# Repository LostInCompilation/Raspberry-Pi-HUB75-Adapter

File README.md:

# Raspberry Pi Zero HUB75 LED-Matrix Controller / Adapter

## Features
- Everything on board
- 2 parralel chains of LED-Matrix panels (each chain can habe many panels)
- Suppport for HUB75 and HUB75E (ABCD**E** address lines)
- Power for LED-Matrix panels comes from board
- I2C extension port for custom hardware (light sensor, accelrometer, ...)
- Reverse polarity protection

## 3D Board view

## Board

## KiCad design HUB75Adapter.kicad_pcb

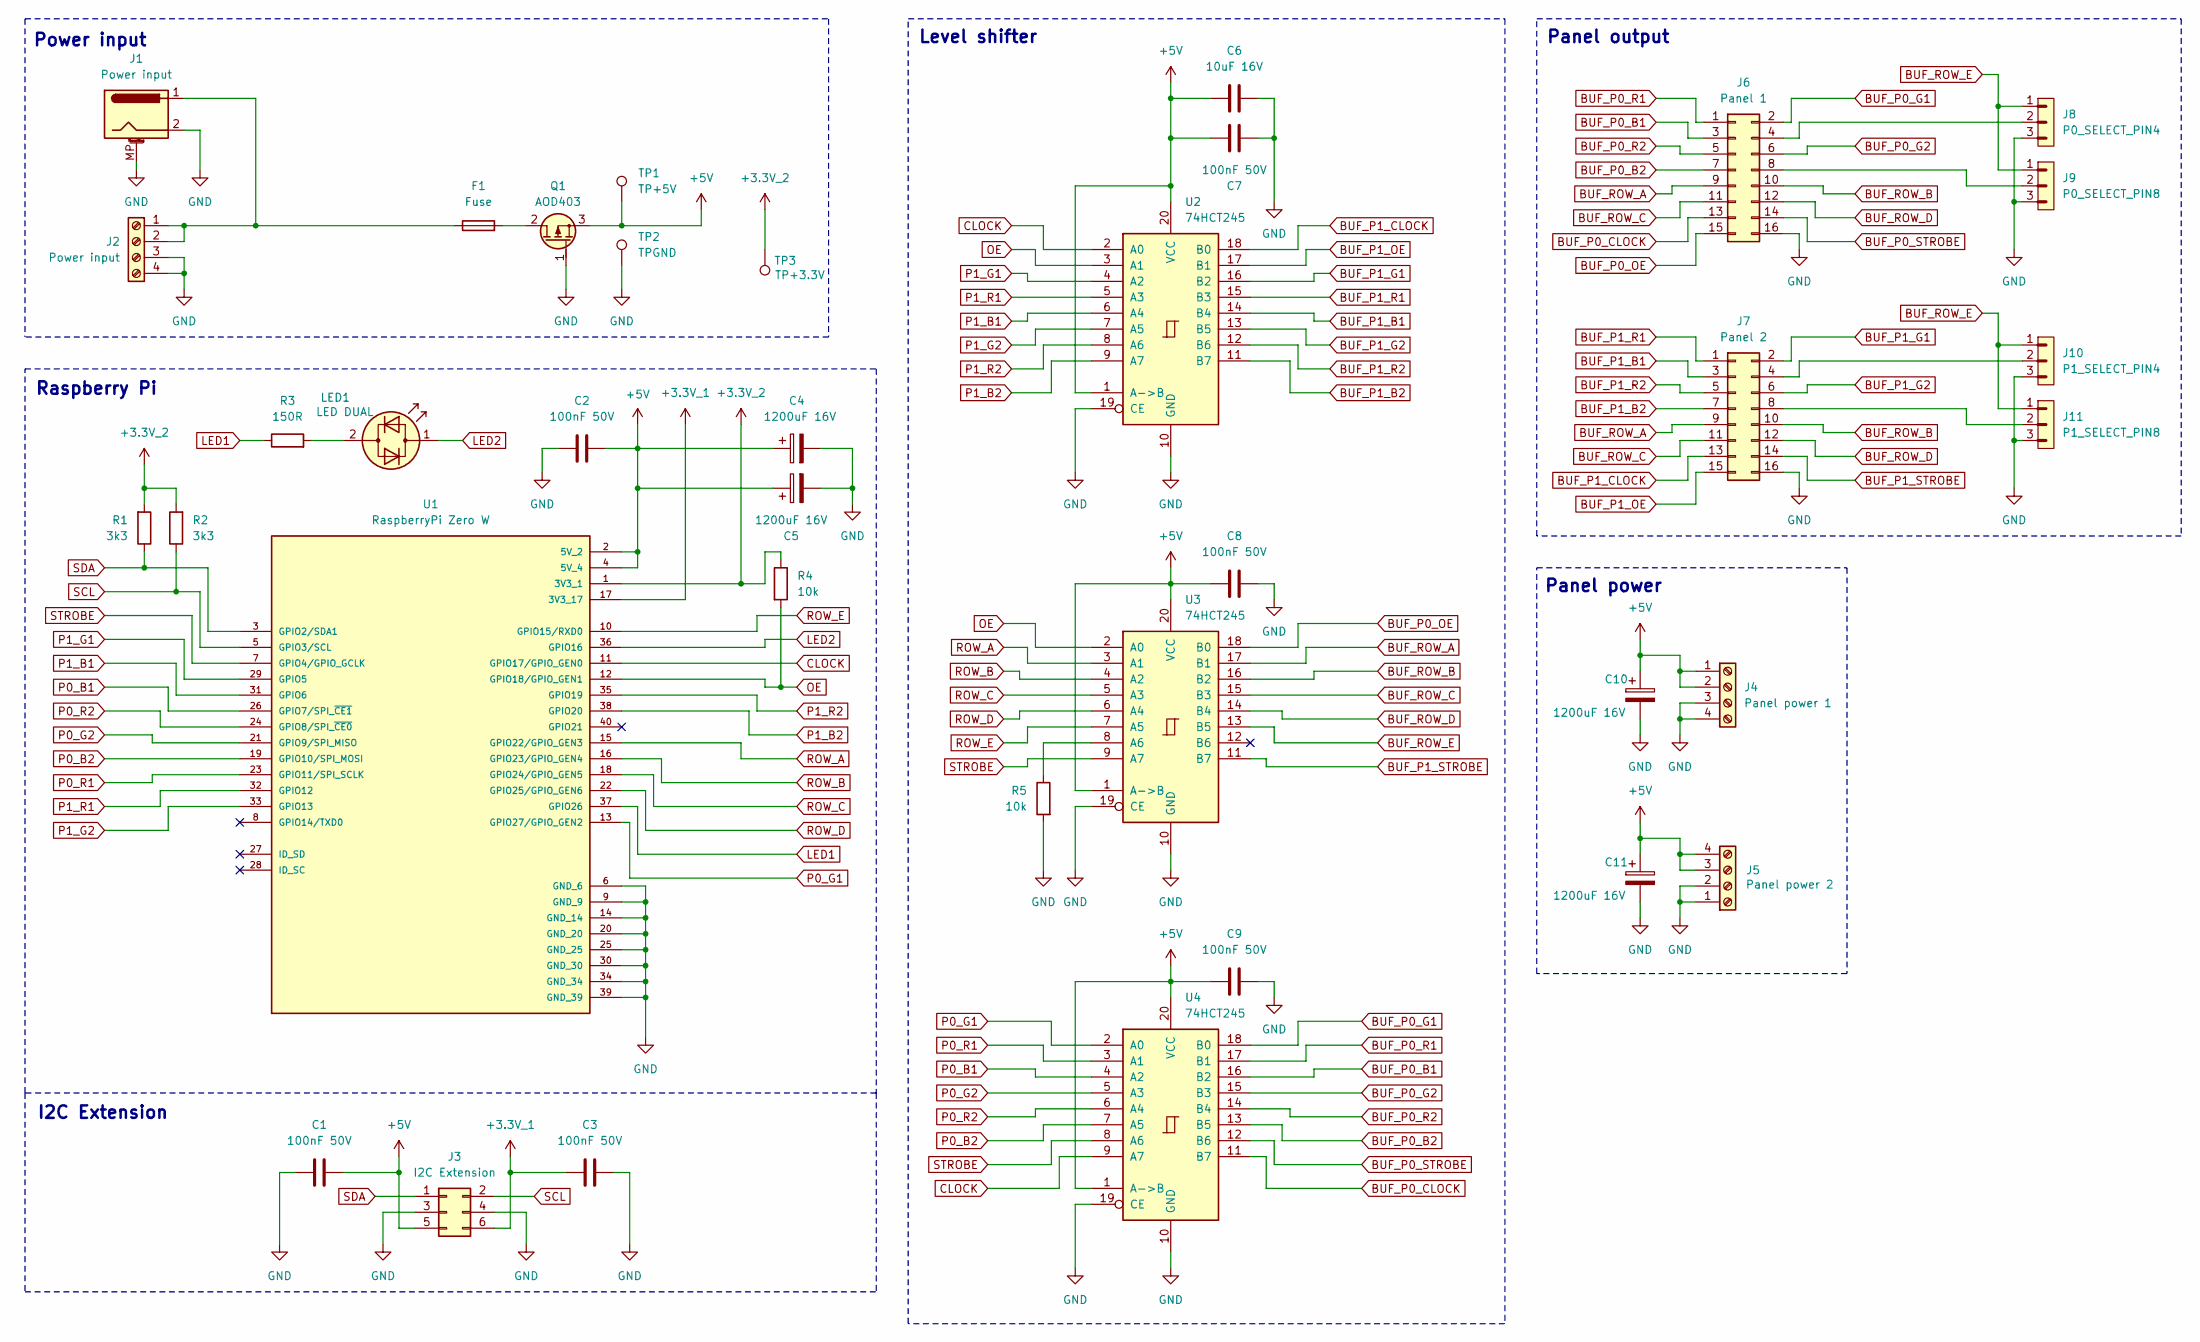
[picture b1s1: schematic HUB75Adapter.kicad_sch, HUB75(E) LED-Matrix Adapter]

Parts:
C1, C2, C3, C7, C8, C9: 100nF 50V; C_1206_3216Metric_Pad1.42x1.75mm_HandSolder
C4, C5, C10, C11: 1200uF 16V; CP_Radial_D10.0mm_P5.00mm
C6: 10uF 16V; C_1206_3216Metric_Pad1.42x1.75mm_HandSolder
F1: Fuse; Fuseholder_Littelfuse_Nano2_154x
J1: Power input; BarrelJack_Horizontal
J2: Power input; TerminalBlock_Phoenix_MKDS-1,5-4_1x04_P5.00mm_Horizontal
J3: I2C Extension; IDC-Header_2x03_P2.54mm_Vertical
J4: Panel power 1; TerminalBlock_Phoenix_MKDS-1,5-4_1x04_P5.00mm_Horizontal
J5: Panel power 2; TerminalBlock_Phoenix_MKDS-1,5-4_1x04_P5.00mm_Horizontal
J6: Panel 1; IDC-Header_2x08_P2.54mm_Vertical
J7: Panel 2; IDC-Header_2x08_P2.54mm_Vertical
J8: P0_SELECT_PIN4; PinHeader_1x03_P2.54mm_Vertical
J9: P0_SELECT_PIN8; PinHeader_1x03_P2.54mm_Vertical
J10: P1_SELECT_PIN4; PinHeader_1x03_P2.54mm_Vertical
J11: P1_SELECT_PIN8; PinHeader_1x03_P2.54mm_Vertical
LED1: LED DUAL; LED_D3.0mm_BiDir
Q1: AOD403; TO-252-2
R1, R2: 3k3; R_1206_3216Metric_Pad1.42x1.75mm_HandSolder
R3: 150R; R_1206_3216Metric_Pad1.42x1.75mm_HandSolder
R4, R5: 10k; R_1206_3216Metric_Pad1.42x1.75mm_HandSolder
TP1: TP+5V; TestPoint_Pad_D1.0mm
TP2: TPGND; TestPoint_Pad_D1.0mm
TP3: TP+3.3V; TestPoint_Pad_D1.0mm
U1: RaspberryPi Zero W; RaspberryPi Zero; PARTREV April 2024
U2, U3, U4: 74HCT245; DIP-20_W7.62mm_LongPads

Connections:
+3.3V_1: C3.2, J3.6, U1.17 (3V3_17)
+3.3V_2: R1.2, R2.2, R4.1, TP3.1, U1.1 (3V3_1)
+5V: C1.1, C2.2, C4.1, C5.1, C6.1, C7.1, C8.1, C9.1, C10.1, C11.1, J3.5, J4.1, J4.2, J5.3, J5.4, Q1.3 (S), TP1.1, U1.2 (5V_2), U1.4 (5V_4), U2.1 (A->B), U2.20 (VCC), U3.1 (A->B), U3.20 (VCC), U4.1 (A->B), U4.20 (VCC)
BUF_P0_B1: J6.3, U4.16 (B2)
BUF_P0_B2: J6.7, U4.13 (B5)
BUF_P0_CLOCK: J6.13, U4.11 (B7)
BUF_P0_G1: J6.2, U4.18 (B0)
BUF_P0_G2: J6.6, U4.15 (B3)
BUF_P0_OE: J6.15, U3.18 (B0)
BUF_P0_R1: J6.1, U4.17 (B1)
BUF_P0_R2: J6.5, U4.14 (B4)
BUF_P0_STROBE: J6.14, U4.12 (B6)
BUF_P1_B1: J7.3, U2.14 (B4)
BUF_P1_B2: J7.7, U2.11 (B7)
BUF_P1_CLOCK: J7.13, U2.18 (B0)
BUF_P1_G1: J7.2, U2.16 (B2)
BUF_P1_G2: J7.6, U2.13 (B5)
BUF_P1_OE: J7.15, U2.17 (B1)
BUF_P1_R1: J7.1, U2.15 (B3)
BUF_P1_R2: J7.5, U2.12 (B6)
BUF_P1_STROBE: J7.14, U3.11 (B7)
BUF_ROW_A: J6.9, J7.9, U3.17 (B1)
BUF_ROW_B: J6.10, J7.10, U3.16 (B2)
BUF_ROW_C: J6.11, J7.11, U3.15 (B3)
BUF_ROW_D: J6.12, J7.12, U3.14 (B4)
BUF_ROW_E: J8.1, J9.1, J10.1, J11.1, U3.13 (B5)
CLOCK: U1.11 (GPIO17/GPIO_GEN0), U2.2 (A0), U4.9 (A7)
GND: C1.2, C2.1, C3.1, C4.2, C5.2, C6.2, C7.2, C8.2, C9.2, C10.2, C11.2, J1.2, J1.MP (MountPin), J2.3, J2.4, J3.3, J3.4, J4.3, J4.4, J5.1, J5.2, J6.16, J7.16, J8.3, J9.3, J10.3, J11.3, Q1.1 (G), R5.2, TP2.1, U1.6 (GND_6), U1.9 (GND_9), U1.14 (GND_14), U1.20 (GND_20), U1.25 (GND_25), U1.30 (GND_30), U1.34 (GND_34), U1.39 (GND_39), U2.10 (GND), U2.19 (CE), U3.10 (GND), U3.19 (CE), U4.10 (GND), U4.19 (CE)
LED1: R3.1, U1.37 (GPIO26)
LED2: LED1.1 (KA), U1.36 (GPIO16)
unnamed: F1.1, J1.1, J2.1, J2.2
unnamed: J6.4, J8.2
unnamed: J6.8, J9.2
unnamed: J7.4, J10.2
unnamed: J7.8, J11.2
unnamed: LED1.2 (AK), R3.2
unnamed: F1.2, Q1.2 (D)
unnamed: R5.1, U3.8 (A6)
OE: R4.2, U1.12 (GPIO18/GPIO_GEN1), U2.3 (A1), U3.2 (A0)
P0_B1: U1.26 (GPIO7/SPI_~CE1), U4.4 (A2)
P0_B2: U1.19 (GPIO10/SPI_MOSI), U4.7 (A5)
P0_G1: U1.13 (GPIO27/GPIO_GEN2), U4.2 (A0)
P0_G2: U1.21 (GPIO9/SPI_MISO), U4.5 (A3)
P0_R1: U1.23 (GPIO11/SPI_SCLK), U4.3 (A1)
P0_R2: U1.24 (GPIO8/SPI_~CE0), U4.6 (A4)
P1_B1: U1.31 (GPIO6), U2.6 (A4)
P1_B2: U1.38 (GPIO20), U2.9 (A7)
P1_G1: U1.29 (GPIO5), U2.4 (A2)
P1_G2: U1.33 (GPIO13), U2.7 (A5)
P1_R1: U1.32 (GPIO12), U2.5 (A3)
P1_R2: U1.35 (GPIO19), U2.8 (A6)
ROW_A: U1.15 (GPIO22/GPIO_GEN3), U3.3 (A1)
ROW_B: U1.16 (GPIO23/GPIO_GEN4), U3.4 (A2)
ROW_C: U1.18 (GPIO24/GPIO_GEN5), U3.5 (A3)
ROW_D: U1.22 (GPIO25/GPIO_GEN6), U3.6 (A4)
ROW_E: U1.10 (GPIO15/RXD0), U3.7 (A5)
SCL: J3.2, R2.1, U1.5 (GPIO3/SCL)
SDA: J3.1, R1.1, U1.3 (GPIO2/SDA1)
STROBE: U1.7 (GPIO4/GPIO_GCLK), U3.9 (A7), U4.8 (A6)

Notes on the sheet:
Raspberry Pi
I2C Extension
Power input
Panel output
Level shifter
Panel power

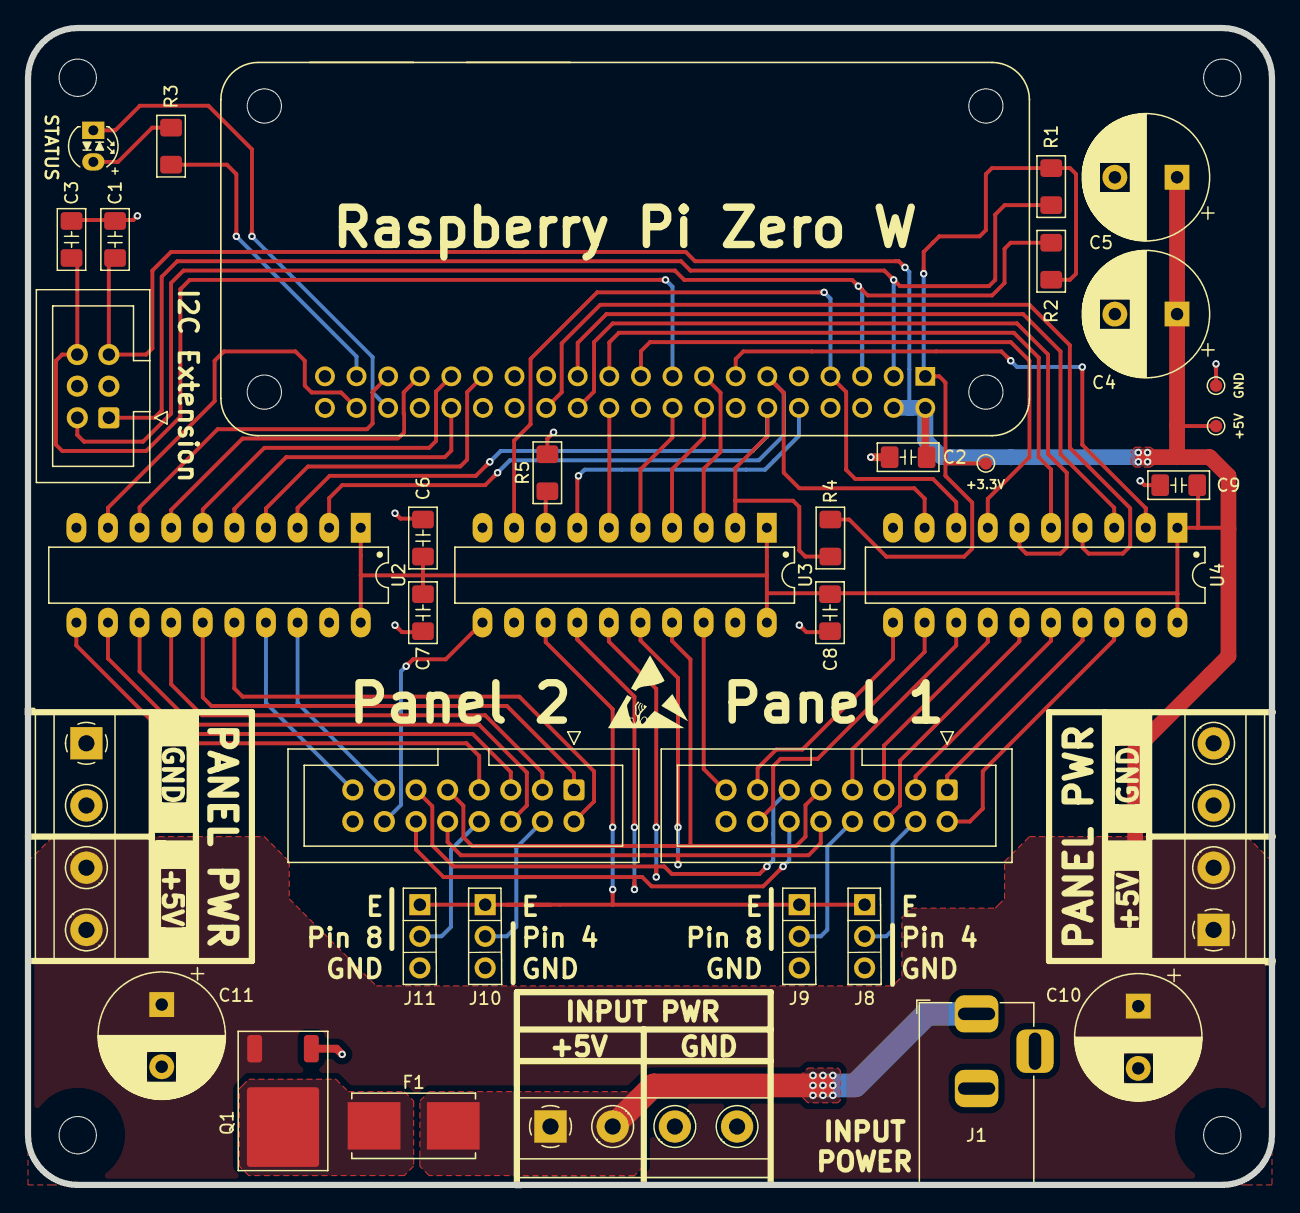
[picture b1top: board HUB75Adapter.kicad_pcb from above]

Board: 2 copper layers, 100.0 x 93.0 mm, 37 parts (0 on the bottom side), 59 nets.

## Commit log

2025-02-10 Add README. Board updates.
2025-02-10 Finish board
2025-02-10 Added serial number to board
2025-02-10 Added plots and BOM
2025-02-11 Added plots
2025-10-29 PCB updates
2025-11-21 Added software folder with code for controlling LED on PCB

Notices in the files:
HUB75Adapter.kicad_pcb:
©2025 Marc Schöndorf
